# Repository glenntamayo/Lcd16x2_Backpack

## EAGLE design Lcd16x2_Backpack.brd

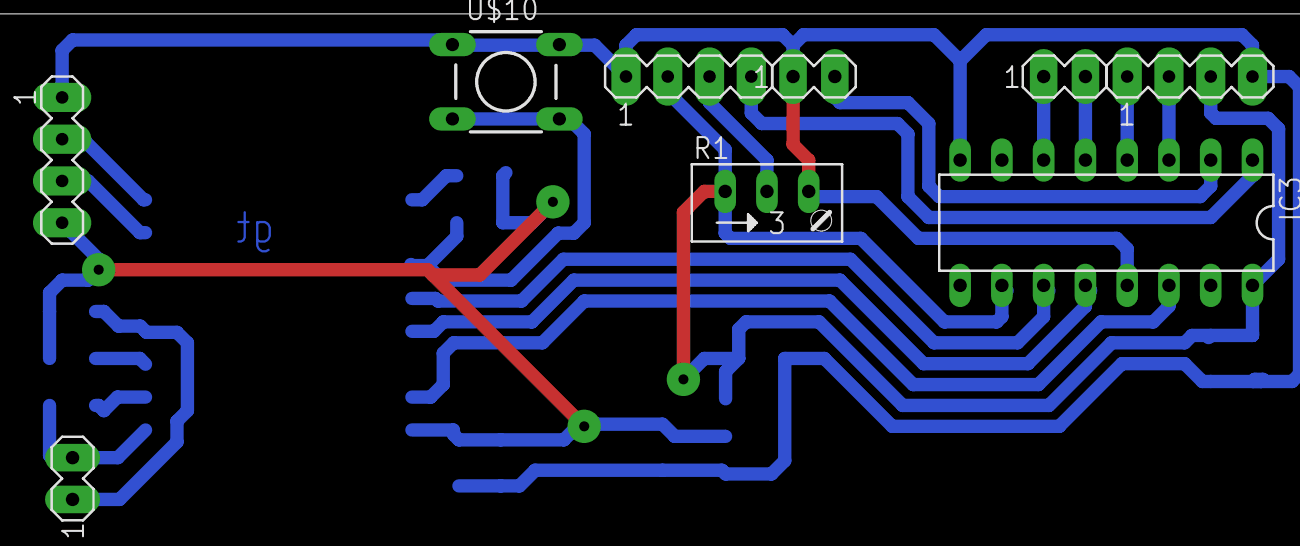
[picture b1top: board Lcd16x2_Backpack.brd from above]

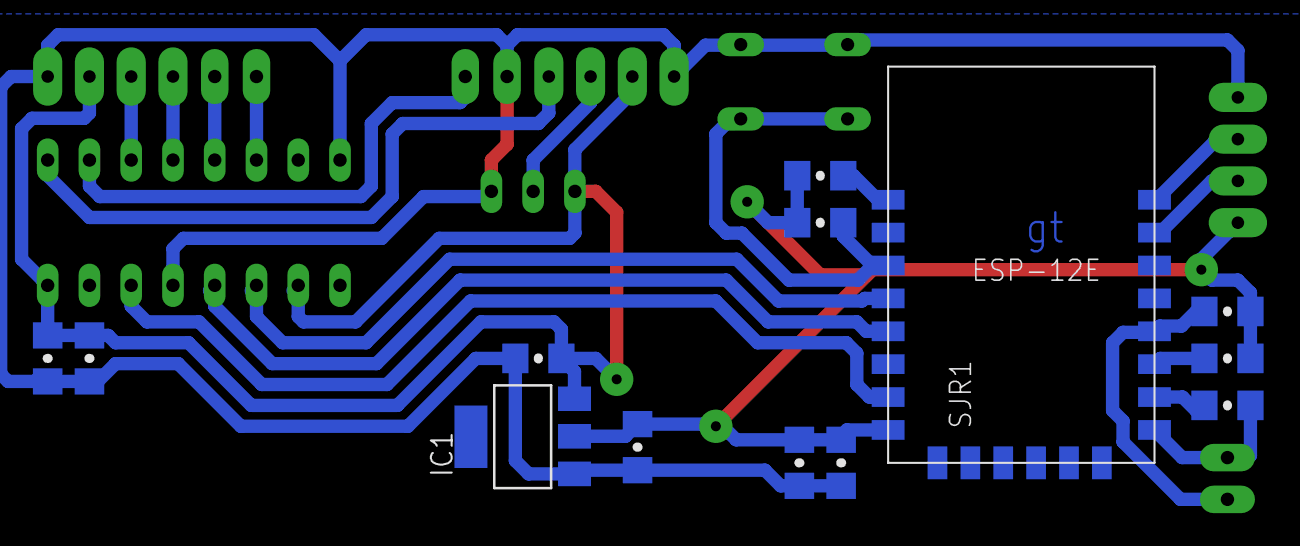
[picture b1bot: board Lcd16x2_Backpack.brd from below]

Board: 2 copper layers, 22 parts (13 on the bottom side), 20 nets.

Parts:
IC1: REG1117; SOT223
IC3: 74HCT595N; DIL16
R1: RJ9W
SJR1: ESP8266-ESP12E
U$1, U$5, U$6, U$7, U$8: RESISTOR-0.41206; 1206
U$2, U$9, U$15: HEADER-4PIN
U$10: SWITCH-MOMENTARY; TACTILE-6X6
U$11, U$14, U$23: HEADER-2PINA; HEADER-2PIN
U$12, U$13, U$16, U$17, U$21, U$22: CAPACITOR-0.2-CER1206; 1206

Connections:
3V3: IC1.2, SJR1.8, U$5.2, U$6.2, U$7.2, U$8.2, U$9.4, U$13.2, U$16.2, U$17.2
595RCK: IC3.12, SJR1.5
595SCK: IC3.11, SJR1.4
595SER: IC3.14, SJR1.7
DB4: IC3.6, U$14.1
DB5: IC3.5, U$14.2
DB6: IC3.4, U$2.1
DB7: IC3.3, U$2.2
EN: IC3.2, U$23.2
GND: IC1.1, IC3.8, IC3.13, R1.A, SJR1.9, U$1.1, U$2.4, U$9.1, U$10.1, U$10.2, U$11.2, U$12.1, U$13.1, U$15.1, U$16.1, U$17.1, U$21.2, U$22.2, U$23.1
unnamed: SJR1.12, U$5.1, U$11.1
unnamed: SJR1.11, U$6.1
unnamed: SJR1.10, U$1.2
unnamed: SJR1.1, U$8.1
unnamed: SJR1.3, U$7.1, U$10.3, U$10.4
POT-B: R1.S, U$15.3
RS: IC3.1, U$15.4
RX: SJR1.15, U$9.3
TX: SJR1.16, U$9.2
VCC: IC1.3, IC3.10, IC3.16, R1.E, U$2.3, U$12.2, U$15.2, U$21.1, U$22.1

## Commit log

2019-03-25 Initial
2019-03-25 Production 1
